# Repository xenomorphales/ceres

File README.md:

# Cérès

Cérès est le robot secondaire à roues de l'association Xenomorphales. Le but
premier de notre association étant de participer à la coupe de France de
robotique, ce robot respecte les contraintes imposées au robot secondaire, et
notamment, la contrainte de périmètre.

L'ensemble du robot, que ce soit les modèles mécaniques, les schématiques et
les routages électroniques tout comme les codes sources, tout est sous licence
GPLv3. Libre donc à vous tous de donner vie à ce petit robot de vos propres
mains (et gouttes de sueur) et de vous amuser avec ou d'en apprendre plus sur
la robotique. Nous serions ravis que vous nous partagiez vos expériences avec
nos robots.

Vous pouvez retrouver toute notre actualité ou apprendre à nous connaître sur
notre site internet : http://xenomorphales.org/

## Crédits

- [TheFox/GPLv3.md](https://github.com/TheFox/GPLv3.md) (commit c81a2af) :
pour la GPLv3 en Markdown. C'est plus lisible à lire sur GitHub.

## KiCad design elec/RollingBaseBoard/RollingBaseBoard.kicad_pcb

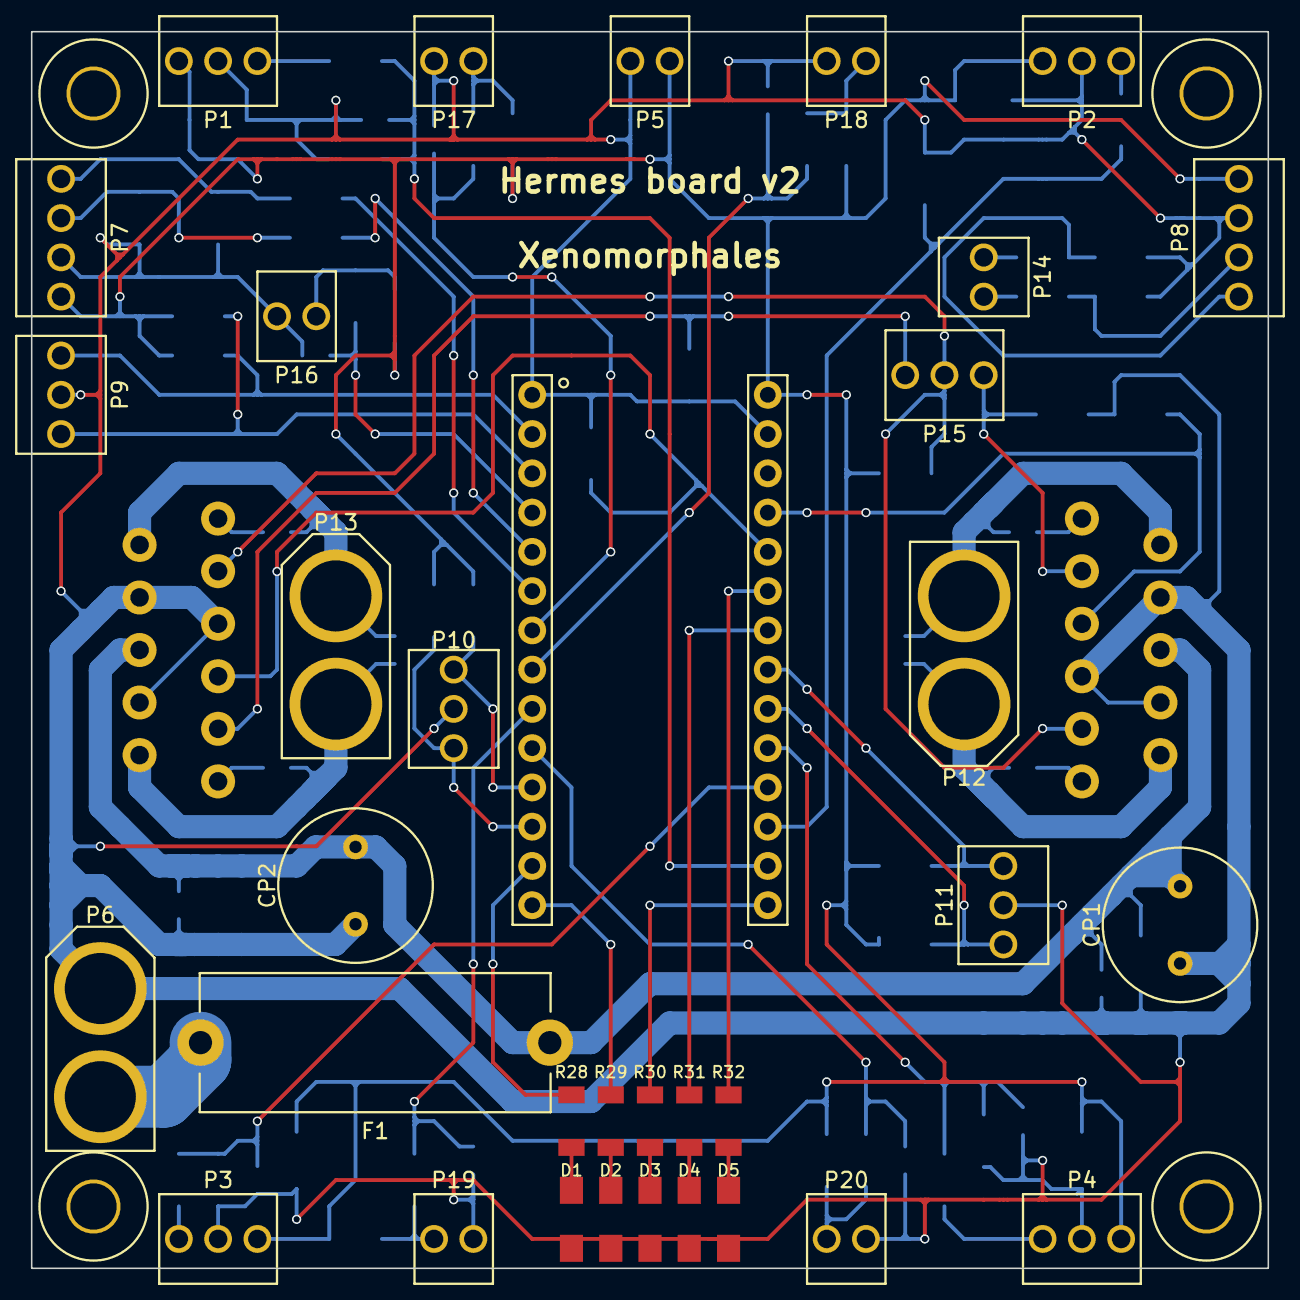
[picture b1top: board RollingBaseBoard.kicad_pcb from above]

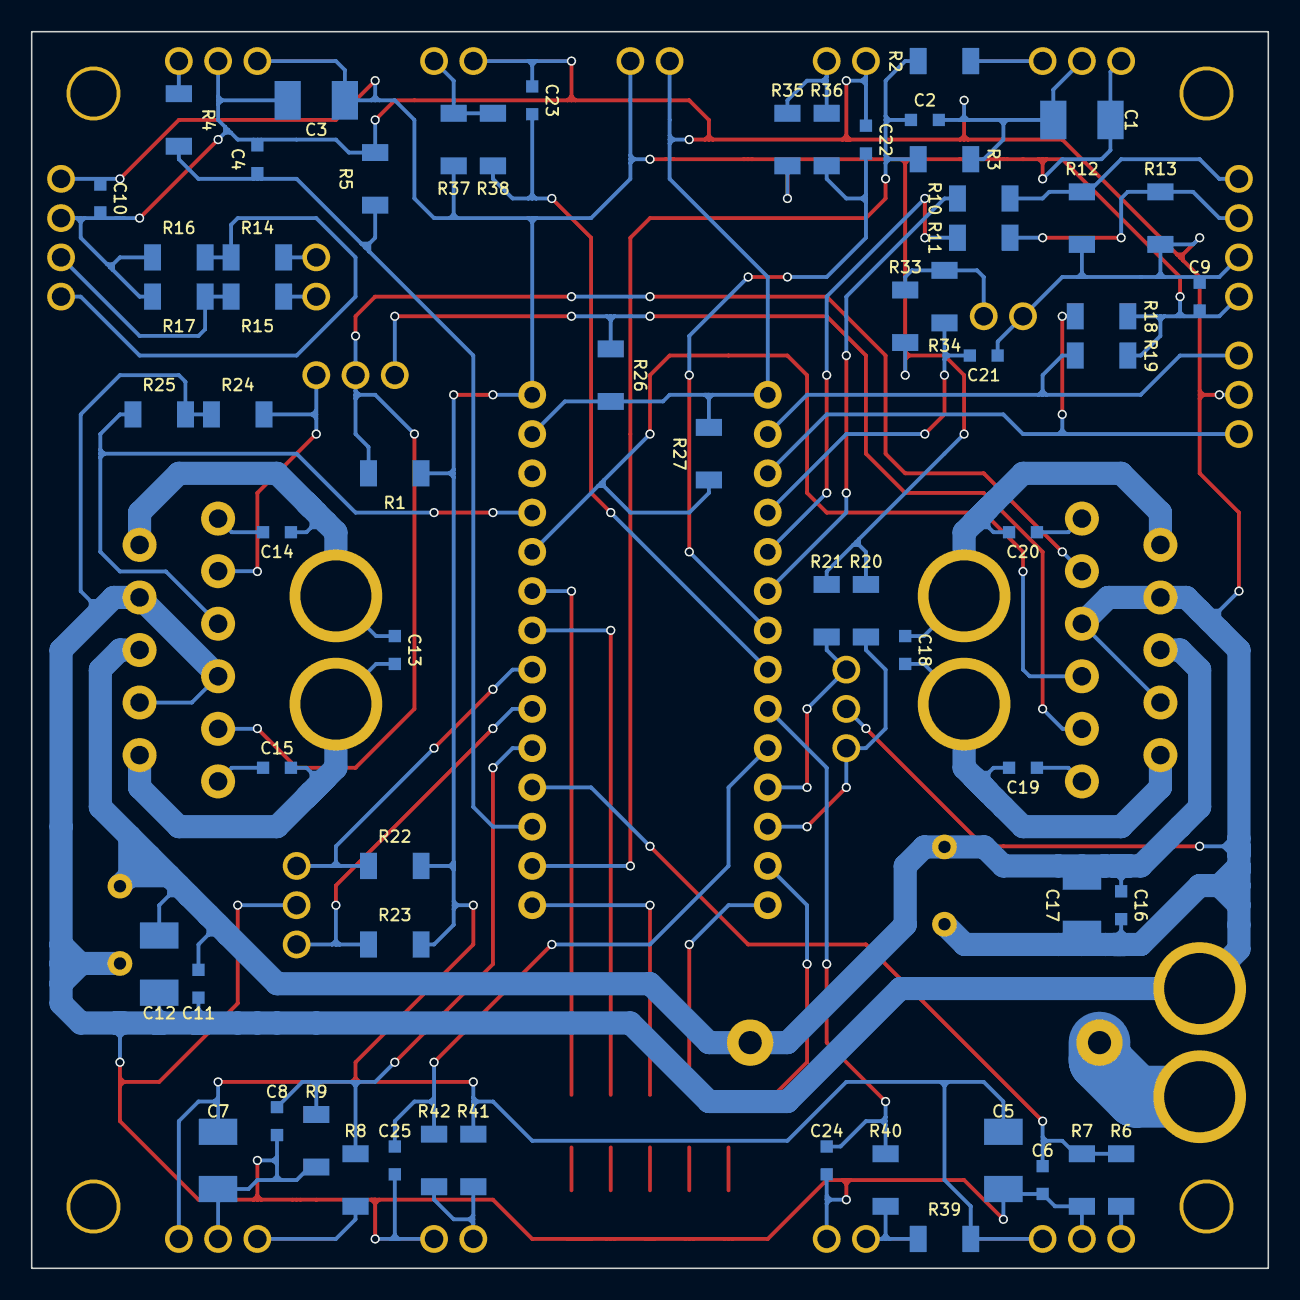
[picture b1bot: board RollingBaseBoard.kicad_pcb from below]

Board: 2 copper layers, 80.0 x 80.0 mm, 98 parts (62 on the bottom side), 59 nets.

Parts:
C1, C3, C5, C7, C12, C17: 10µF; C_CMS1210
C2, C4, C6, C8, C9, C10, C11, C16: 100nF; C_CMS0603
C13, C18: 1nF; C_CMS0603
C14, C15, C19, C20: 10nF; C_CMS0603
C21, C22, C23, C24, C25: 1µF; C_CMS0603
CP1, CP2: 330µF; C_Radial
D1, D2, D3, D4, D5: LED_Green; LED_Green_CMS
F1: FUSE; Fuse
P1, P2, P3, P4: GP2; Conn_01x03
P5: Bat5V; Conn_01x02
P6: Bat15V; Power_Conn_01x02
P7, P8: Encoder; Conn_01x04
P9: UART_1; Conn_01x03
P10: UART_2; Conn_01x03
P11: I2C; Conn_01x03
P12, P13: Motor; Power_Conn_01x02
P14: Encoder2; Conn_01x02
P15: Motor; Conn_01x03
P16, P17, P18, P19, P20: Switch; Conn_01x02
R1, R2, R4, R6, R8, R12, R13, R16, R17, R18, R19, R20, R21, R22, R23, R24, R25, R26, R27: 10kΩ; R_CMS1206
R3, R5, R7, R9: 20kΩ; R_CMS1206
R10, R11, R14, R15: 22Ω; R_CMS1206
R28, R29, R30, R31, R32: 82Ω; R_CMS1206
R33, R35, R37, R39, R41: 100kΩ; R_CMS1206
R34, R36, R38, R40, R42: 18kΩ; R_CMS1206
U1, U2: LMD18201
U3: Teensy3.1

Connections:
/Com/+5V: C1.2, C3.2, C5.2, C7.2, C9.2, C10.2, P1.3, P2.3, P3.3, P4.3, P5.2, P7.1, P8.1, R1.2, R18.1, R19.1, R20.1, R21.1, R22.1, R23.1, R33.1, R35.1, R37.1, R39.1, R41.1, U3.90
/Com/GND: C1.1, C2.1, C3.1, C4.1, C5.1, C6.1, C7.1, C8.1, C9.1, C10.1, C11.2, C12.2, C16.2, C17.2, C21.2, C22.2, C23.2, C24.2, C25.2, CP1.2, CP2.2, D1.1, D2.1, D3.1, D4.1, D5.1, P1.2, P2.2, P3.2, P4.2, P5.1, P6.1, P7.2, P8.2, P9.2, P10.2, P11.2, P16.1, P17.1, P18.1, P19.1, P20.1, R3.1, R5.1, R7.1, R9.1, R12.1, R13.1, R16.1, R17.1, R24.1, R25.1, R26.1, R27.1, U1.4, U1.7, U1.8, U2.4, U2.7, U2.8, U3.91, U3.92
/Com/RX1: P9.3, R19.2, U3.0
/Com/RX2: P10.3, R21.2, U3.9
/Com/SCL: P11.1, R22.2, U3.19
/Com/SDA: P11.3, R23.2, U3.18
/Com/TX1: P9.1, R18.2, U3.1
/Com/TX2: P10.1, R20.2, U3.10
/Driver_1/+15V: C11.1, C12.1, C16.1, C17.1, CP1.1, CP2.1, F1.1, U1.6, U2.6
/Driver_1/Direction: P15.3, R24.2, U1.3
/Driver_1/PWM: R25.2, U1.5, U3.23
/Driver_1/ThermalFlag: P15.2, R1.1, U1.9, U2.9
/Driver_2/Direction: P15.1, R26.2, U2.3
/Driver_2/PWM: R27.2, U2.5, U3.22
/Encoder_1/A: R11.1, U3.3
/Encoder_1/B: R10.1, U3.4
/Encoder_2/A: P14.1, R15.1
/Encoder_2/B: P14.2, R14.1
/Teensy/GP2_1: C2.2, R2.1, R3.2, U3.14
/Teensy/GP2_2: C4.2, R4.1, R5.2, U3.15
/Teensy/GP2_3: C6.2, R6.1, R7.2, U3.16
/Teensy/GP2_4: C8.2, R8.1, R9.2, U3.17
/Teensy/LimitSwitch1: C22.1, R36.1, U3.5
/Teensy/LimitSwitch2: C23.1, R38.1, U3.6
/Teensy/LimitSwitch3: C24.1, R40.1, U3.7
/Teensy/LimitSwitch4: C25.1, R42.1, U3.8
/Teensy/Pull: C21.1, R34.1, U3.2
unnamed: C13.1, C15.1, P12.1, U1.10
unnamed: C13.2, C14.2, P12.2, U1.2
unnamed: C14.1, U1.1
unnamed: C15.2, U1.11
unnamed: C18.1, C20.1, P13.1, U2.10
unnamed: C18.2, C19.2, P13.2, U2.2
unnamed: C19.1, U2.1
unnamed: C20.2, U2.11
unnamed: D1.2, R28.2
unnamed: D2.2, R29.2
unnamed: D3.2, R30.2
unnamed: D4.2, R31.2
unnamed: D5.2, R32.2
unnamed: F1.2, P6.2
unnamed: P1.1, R2.2
unnamed: P2.1, R4.2
unnamed: P3.1, R6.2
unnamed: P4.1, R8.2
unnamed: P7.3, R11.2, R13.2
unnamed: P7.4, R10.2, R12.2
unnamed: P8.3, R15.2, R17.2
unnamed: P8.4, R14.2, R16.2
unnamed: P16.2, R33.2, R34.2
unnamed: P17.2, R35.2, R36.2
unnamed: P18.2, R37.2, R38.2
unnamed: P19.2, R39.2, R40.2
unnamed: P20.2, R41.2, R42.2
unnamed: R28.1, U3.11
unnamed: R29.1, U3.12
unnamed: R30.1, U3.13
unnamed: R31.1, U3.20
unnamed: R32.1, U3.21

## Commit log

2015-05-13 Added STM32Cube and aversive--
2015-05-13 Added test_asserv project
2015-05-13 Added gitignore
2015-06-22 After Eurobot (France) 2015 contest
2015-06-22 Moved sources. Added missing gp2 drivers.
2015-06-22 Added 2015 meca
2015-06-22 Added some new meca components
2015-06-22 Added meca gitignore
2015-06-22 Renamed encoder because of wrong vendor name
2015-07-19 Begin meca v2016.
2015-08-03 Added new poulie (conrad)
2015-08-03 Added vis
2015-08-03 (meca) Added patin
2015-08-03 (meca) Added motors.
2015-08-03 Added batteries.
2015-08-04 (meca) Test batteries.
2015-08-04 (meca) New batteries tests.
2015-08-27 Wheel base improvement.
2015-09-12 Added tendeur.
2015-09-15 Improved tendeur
2015-09-15 Improved Odometer Base
2015-09-23 Adding schematic of the rolling base board
2015-09-25 Adding footprints for the rolling base board
2015-09-26 Adding missing power connector footprint
2015-09-26 Updated the schematics to use the proper footprints.
    Also regenerated the net list file.
2015-09-28 Starting rolling base board's routing
2015-09-29 Progressing on rolling base board's routing
2015-09-30 Replacing M4 screws with M3 ones
2015-10-06 Progressing on the rolling base board
2015-10-07 Improving a few footprints
2015-10-08 Completing rolling base board, only a few minor fixes are left to do
2015-10-11 Fixing rolling base board routing's right angles
2015-10-11 Adding all the missing refs on rolling base board routing
2015-10-11 Minor fix to rolling base board routing
2015-10-11 Finished tendeur
2015-10-13 Updated rolling base board CMS footprints to actually have room to solder them
2015-10-17 Added bumpers and gp2 sensors
2015-10-17 Finished rolling base
2015-10-25 Fixing rolling base board routing after footprints change.
2015-10-25 Optimising rolling base board routing a bit
    Reduced via count by 6
2015-10-28 Optimising rolling base board routing some more. Also removing a GND loop.
2015-10-28 The rolling base board now has a name. Please welcome Hermes in the family.
2015-11-17 Fixing Hermes footprints and routing, bumped to v2.
2015-11-18 Final checks and fixes to Hermes v2
    It's now ready for production.
2015-11-19 Finally adding license and readme files
2015-11-19 Moving elec/RollingBaseBoard to elec/Hermes
2015-11-19 Adding component list for Hermes
2016-01-08 Removing old software and just adding the readme for hermes software.
2017-01-23 Finally adding Hermes 2016 software
2017-04-03 begining v2017 with RIOT
2017-04-04 improved motors pwm command
2017-04-17 added feetech dynamixel, debug gyro and xtimer collision
2017-04-17 arm state test
2017-04-27 added second arm
2017-05-02 added v2017 board schematics
2017-05-02 begining clean arm.c
2017-05-02 added scheduler + arm_update (not tested)
2017-05-03 Arm state machine working
2017-05-03 Updated v2017 schematics and added its Components.md
2017-05-03 Added robot controller
2017-05-11 added pull and gp2
2017-05-11 added boards dir to copy specific board implementation
2017-05-11 moved robot_drivers into a separate module
2017-05-11 fix files that were not moved
2017-05-15 integration test
2017-05-18 added locator (not tested)
2017-05-18 added cartesian (not tested)
2017-05-18 added c++ management in headers
2017-05-18 added Action and CalibrateAction (not tested)
2017-05-19 c++ (dirty)
2017-05-20 added shell
2017-05-20 added cmd_device
2017-05-21 added gyro config
2017-05-21 gcc 4.8 compat (for rasp)
2017-05-21 new arm retracted pose
2017-05-21 new arm retracted pose (fix)
2017-05-21 added cmd_test_speed
2017-05-21 added robot config + first attempt to calibrate robot
2017-05-21 debug dist integration
2017-05-21 new robot calibration + debug negative speed
2017-05-21 added grip and funny interfaces (not implemented)
2017-05-22 added funny + servobus
2017-05-22 improved funny
2017-05-22 debug locator ?
2017-05-22 arm disabled at init
2017-05-22 debug robot angle
2017-05-22 added cartesian dev
2017-05-22 improved cartesian
2017-05-23 homologation
2017-05-23 c++11
2017-05-23 debug homologation
2017-05-23 add robot.distance dev
2017-05-30 add cmd_dxl
2017-05-30 servo retracted pose
2017-05-30 added Match
2017-05-30 grip
2017-05-30 wait 20 sec at begining of match
2017-05-30 implement arm set angle
2017-05-30 grip max torque
2017-05-30 added grip hold
2017-05-30 add arm cmd
2017-05-30 side
2017-05-30 grip debug
2017-05-30 grip pose
2017-05-30 new strat
